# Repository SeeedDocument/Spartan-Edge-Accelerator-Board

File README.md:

---
name: Spartan Edge Accelerator Board
category: Platform
bzurl: 
oldwikiname: 
prodimagename:
surveyurl: 
sku: 102030005
tags:
---

The Spartan Edge Accelerator Board (SEA Board in short) is a lightweight FPGA development board, it is based on the Xilinx Spartan-7 chip and follows the Arduino shield form factor. Hence, you can use it as an Arduino shield to driver an LCD and a camera or as a stand-alone FPGA development board. Besides, with the help of on-board ESP32 chip, the SEA board also enables your Arduino with WiFi and Bluetooth function.

**Spartan-7** is the newest and most cost-effective FPGA chip among Xilinx’s FPGA family, offers the best in class performance per watt. 

On top of that, we provide the full FPGA APIs for Arduino, which means Arduino users are able to use the FPGA function without knowing anything about FPGA. This board will broaden Arduino’s capability in many ways like simple image processing and computer vision application, signal encryption and decryption, and signal sampling and processing. 

## Features

- Full FPGA APIs for Arduino
- Stand alone mode/Arduino Shield mode
- On-board WiFi and bluetooth 4.1 with BLE
- On-board 8 bit ADC
- On-board 6 axis Accelerometer and Gyroscope
- On-board Grove Connector(I2C/D2)

## Specification

|Parameter|Value|
|---|---|
|**FPGA**||
|FPGA Chip|Spartan-7 XC7S15|
|Logic Cells|12,800|
|Slics|2000|
|CLB Flip-Flops|16,000|
|Max. Distributed RAM (Kb)|150|
|Block RAM/FIFO w / ECC (36 kb each)|10|
|Total Block RAM (Kb)|360|
|Clock Mgmt Tiles (1 MMCM + 1 PLL)|2|
|DSP Slices|20|
|**Wireless**||
|Wireless Chip|Espressif ESP32-D0WDQ6|
|WiFi |802.11 b/g/n 2.4GHz|
|Bluetooth|Bluetooth 4.1 with BLE|
|**Peripheral**||
|Video|Mini HDMI x1|
|Camera|CSI/MIPI interface x1 (compatible with Raspberry Pi Camera V1 - OV5640)|
|SD card|Micro SD/TF card slot x1|
|FPGA GPIO|10 pins header (IO9~IO0)|
|Arduino GPIO|32 pins header (Arduino form factor)|
|Grove|Grove Connector x2 (I2C/D2)|
|LED|Monochrome LED x2<br>RGB LED x2|
|Button|Boot x1<br> Reset x1<br> FPGA Reset x1 <br> User x2|
|Switch|Power Mode Switch x1<br>5-Channel DIP Switch x1|
|**Power**||
|Operating Voltage|5V|
|Power Mode|USB Type C 5V<br>VIN 5V<br>Arduino VCC 5V|
|**Others**||
|ADC|8 bit ADC1173|
|Accelerometer and Gyroscope|6-axis LSM6DS3TR |

## Hardware Overview

<div align="center">
<figure>
  <a href="https://raw.githubusercontent.com/SeeedDocument/Spartan-Edge-Accelerator-Board/master/img/Spartan-Edge-Accelerater-Board-v1.0-pin.jpg" target="_blank">
  <figcaption><b>Figure 1</b>. <i>Seeed relay quick selection diagram, you can click the diagram to view the original file</i></figcaption></a>
</figure>
</div>

|Number|Detail|
|-----|-------|
|1.|FPGA : XC7S15-1FTGB196C|
|2.|WiFi/Bluetooth : ESP32-D0WDQ6|
|3.|6-axis Accelerometer and Gyroscope : LSM6DS3TR |
|4.|DAC : DAC7311IDCKR|
|5.|Buck-DCDC : TPS62130|
|6.|USB-to-UART : CP2102-GMR|
|7.|USB : Type-C |
|8.|Mini HDMI|
|9.|CSI Interface ：MIPI Camera (compatible with Raspberry Pi Camera V1 - OV5640)|
|10.|Arduino Header : Compatible with Arduino UNO|
|11.|DIP Switchs :|K1-K4 user switchs<br>K5 Switch FPGA Programming Mode  ->JTAG:|
|12.||

based on Spartan-7, one of the newest and most cost-effective chip among Xilinx’s FPGA family. 

<p style=":center"></p>

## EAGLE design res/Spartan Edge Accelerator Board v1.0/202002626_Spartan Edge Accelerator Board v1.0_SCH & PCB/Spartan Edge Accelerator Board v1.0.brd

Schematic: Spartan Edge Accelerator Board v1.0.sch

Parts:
ANT1: ACA-5036; ANT3-SMD-5.2X3.7X0.7MM
BOOT: SKRPABE010; SW4P-SMD-4.5X3.2X2.5MM
BUTTON1, BUTTON2: BUTTON; SW4P-SMD-4.5X3.2X2.5MM
C1, C10, C11, C13, C14, C16, C22, C23, C25, C26, C27, C28, C29, C30, C31, C32, C33, C34, C35, C36, C37, C38, C39, C50, C51, C59, C60, C63, C64, C65, C66, C67, C68, C75: 1uF; C0402
C2, C3: 10pF; C0402
C4, C5, C6, C7, C8, C9, C12, C15, C17, C24, C72, C73, C78, C81, C84, C99, C101, C103, C105: 100nF; C0402
C18, C57, C77, C85, C94: 100nF; C0603
C20: 3.3nF; C0402
C21: 10nF; C0402
C40, C41, C42, C45, C48, C49, C52, C58, C61, C62, C69, C70: 22uF; C1206
C43, C44, C46: 470nF; C0402
C47, C55, C56, C74, C76: 10uF; C0805
C53, C54: 33nF; C0603
C71, C79, C80, C83, C86, C87, C95, C96, C98, C100: DNP; C0402
C82, C102, C104, C106: 10uF; C0603
C90, C93, C97: DNP; C0603
C91, C92: 4.7uF; C0603
D1, D2, D5, D6, D7, D8, D9, D11, D12, D13, D14, D15, D16, D17, D21: ESDPSA0402V05; ESD-0402
D3, D18: Green; LED-0402
D4: RB160M-60TR; SOD-123
D10: BAS16XV2T1G; SOD-523
D19, D20: Red; LED-0402
F1: 1000mA; F1206
F2: 1812L160/12; F1812
FB1, FB2, FB3: 220R/2A; F0603
FB4, FB5: 120R/1.3A; F0402
FB6: BLM21PG331SN1D; F0805
FB7, FB8, FB9: 120R/2A; F0603
FPGA_RST: BUTTON; SW4P-SMD-4.5X3.2X2.5MM
FR1, FR2, FR3, FR4, FR5, FR6: SEEEDSTUDIO-OPEN-SCH-FRAME-BIG; SEEEDSTUDIO-PCB-FRAME
J1: 4PIN-2.54; H4-2.54
J2, J4: 320110033; HW4-2.0
J3: SCHA5B0200; MICRO-SD9+7P-SMD-15X14.5X1.5
J5: 2*3pin; H2X3-2.54
J6: FPC 15pins; H2X15-SMD-1MM
J8: 6PIN-2.54; H6-2.54-C65D35MIL
J9: Mini HDMI; HDMI-19+4P-0.4-11.2X7.5MM
J10: DNP; H10-2.54
J15: HEADER-3P-2.54; H3-2.54
L1, L2: DNP; L0402
L3, L4, L5, L7: DNP; INT4-0.8-2X1.2MM
L6: VLC5045T-2R2N; INT2-SMD-4.8X4.8X3MM
L15: SRF2012-900YA; INT4-0.85-2X1.25X1.2MM
LED1, LED2: SK6805; LED-4P-SMD-2.7X2.4MM
Q1: CJ2102; SOT-323
Q2, Q3: CJ3407; SOT-23
Q4, Q5: MMBT3904; SOT-23
R1, R33, R35, R118, R120, R122, R124, R165: 20k; R0402
R2, R17, R20, R38, R94, R95, R97, R104, R105, R106, R116, R125, R127, R146, R147, R149, R150, R181, R182, R184, R186, R187: DNP; R0402
R3, R6, R7, R16, R23, R24, R25, R26, R27, R37, R47, R58, R66, R93: 0R; R0402
R4, R5, R9, R13, R14, R18, R19, R32, R34, R36, R48, R67, R71, R85, R96, R114, R117, R119, R121, R123, R126, R133, R145, R164, R183, R185: 10k; R0402
R8, R21, R40, R41, R42, R43, R53, R54, R55, R101, R102, R103, R144, R151, R171, R180: 4.7k; R0402
R10, R12, R84, R107, R108, R109, R110, R111, R112, R113, R115, R140, R141, R142, R143: 33R; R0402
R11, R62: 0R; R0603
R15, R22: 5.1k; R0402
R28, R29, R68, R69: 100R; R0402
R30, R31, R44, R45, R46, R153, R155, R157, R159, R161, R163, R167, R173, R175, R177, R179: 2k; R0402
R39: 200k; R0402
R49, R50, R51, R52, R56, R57, R65, R70, R82, R83, R92, R152, R154, R156, R158, R160, R162, R166, R172, R174, R176, R178: 1k; R0402
R59, R60, R63, R64, R130: 100k; R0402
R61: 100k; R0603
R72, R73, R74, R75, R76, R77, R78, R79: 49.9R; R0402
R80, R81, R86, R87, R88, R89, R90, R91: 100nF; R0603
R98, R99, R100: 150R_1%; R0402
R128, R129: 100R_1%; R0402
R134: 536k_1%; R0603
R135: 100K_1%; R0603
R148: DNP; R1206
RST: SKRPADE010; SW4P-SMD-4.5X3.2X2.5MM
SW1: 311010004; SW6-2.54-9.0X3.5X3.2+2.0MM
SW2: DG2788A; MINI-QFN16-0.4-2.6X1.8X0.55MM
SW4: SWITCH-5BIT-DSHP05TSGER; 10P-SMD-7.95X5.4X2.3MM
TP1, TP2: TEST-POINT-35; TP_3535
TP5: TEST-POINT'4545'; TP-D45MIL
U1: XC7S15-1FTGB196C; FTGB196-1.0-15X15X1.46MM
U2: ESP32-D0WDQ6; QFN48G-0.4-6X6MM
U3: W25Q32JVZPIG; SOIC8-1.27-5X4MM
U4: ADC1173; TSSOP24-0.65-7.8X4.4MM
U5: CP2102-GMR; QFN28
U6: DAC7311IDCKR; SC-70-6
U7: CJ1117-3V3; SOT-223
U8: XC6221B102MR; SOT-23-5
U9: RT9013-18GB; SOT-23-5
U10: Arduino pins; ARDUINO-32P
U11: TPS62130; VQFN16-0.5-3X3X1MM
U12: LSM6DS3TR; LGA14L_DOT_INDICATOR
U13: PCA9306DQER; X2SON8-0.35-1.4X1X0.37MM
U15, U16: RCLAMP0524P; ESD10P-0.5-2.5X1X0.58MM
U17, U18: TXS0104EPWR; TSSOP14-0.65-5X4.4MM
USB2: 320010516/ ST-USB-1410; USB2.0-TYPE-C
X2: O3225100MEDA4SC; X4-SMD-3.2X2.5X1MM
X3: XTL581100-M118-080; X4-SMD-2.5X2.0X1.0MM

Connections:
3V3_IMU: C84.1, C97.2, C99.1, FB5.2, R114.2, R117.2, U12.5 (VDDIO), U12.8 (VDD)
ADC_CLK: U1.C5 (IO_L6P_T0_34), U4.12 (CLK)
ADC_D0: U1.J3 (IO_L17N_T2_34), U4.3 (DO(LSB))
ADC_D1: U1.J2 (IO_L15P_T2_DQS_34), U4.4 (D1)
ADC_D2: U1.D12 (IO_L8P_T1_D11_14), U4.5 (D2)
ADC_D3: U1.E12 (IO_L7N_T1_D10_14), U4.6 (D3)
ADC_D4: U1.F12 (IO_L7P_T1_D09_14), U4.7 (D4)
ADC_D5: U1.C11 (IO_L6P_T0_FCS_B_14), U4.8 (D8)
ADC_D6: U1.H11 (IO_L13P_T2_MRCC_14), U4.9 (D6)
ADC_D7: U1.H12 (IO_L13N_T2_MRCC_14), U4.10 (D7(MSB))
ADC_EN: U1.J4 (IO_L17P_T2_34), U4.1 (!OE)
ADC_IN: C87.1, J1.1, U4.19 (VIN)
AGND: C53.1, R11.1, R135.2, U11.6 (AGND)
AR_3V3_EN: Q2.1 (G), Q3.1 (G), R48.1, U1.L13 (IO_L16N_T2_D31_14)
AR_A0: R32.2, U10.19 (PC0/AD0/D14)
AR_A1: R34.2, U10.20 (PC1/AD1/D15)
AR_A2: R36.2, U10.21 (PC2/AD2/D16)
AR_A3: R119.2, U10.22 (PC3/AD3/D17)
AR_A4: R121.2, U10.23 (PC4/AD4/D18/SDA)
AR_A5: R123.2, U10.24 (PC5/AD5/D19/SCL)
AR_D0/RX: R150.1, U10.1 (PD0/D0/RX), U17.11 (B3)
AR_D1/TX: R146.1, U10.2 (PD1/D1/TX), U17.10 (B4)
AR_D2: R152.2, U10.3 (PD2/D2/INT0)
AR_D3: R154.2, U10.4 (PD3/D3/INT1/PWM)
AR_D4: R156.2, U10.5 (PD4/D4)
AR_D5: R158.2, U10.6 (PD5/D5/PWM)
AR_D6: R172.2, U10.7 (PD6/D6/PWM)
AR_D7: R174.2, U10.8 (PD7/D7)
AR_D8: R176.2, U10.9 (PB0/D8)
AR_D9: R178.2, U10.10 (PB1/D9/PWM)
AR_D10: R160.2, U10.11 (PB2/D10/SS/PWM)
AR_D11: R162.2, U10.12 (PB3/D11/MOSI/PWM)
AR_D12: R164.2, U10.13 (PB4/D12/MISO)
AR_D13: R166.2, U10.14 (PB5/D13/SCK)
AR_MISO: J5.1, U18.11 (B3)
AR_MOSI: J5.5, U18.12 (B2)
AR_RESET: J5.3, R187.2, U10.30 (RESET), U18.10 (B4)
AR_SCK: J5.2, U18.13 (B1)
AR_SCL: R151.1, U10.18 (SCL), U17.12 (B2)
AR_SDA: R171.1, U10.17 (SDA), U17.13 (B1)
CHIP_PU: Q4.3 (C), R5.1, RST.1 (A0), RST.2 (A1), U2.9 (CHIP_PU)
D+: D1.2, L15.3, USB2.A6 (A6/DP1), USB2.B6 (B6/DP2)
D-: D2.2, L15.2, USB2.A7 (A7/DN1), USB2.B7 (B7/DN2)
DAC_DIN: U1.L1 (IO_L18N_T2_34), U6.3 (DIN)
DAC_OUT: C86.1, J1.4, U6.6 (VOUT)
DAC_SCLK: U1.M1 (IO_L18P_T2_34), U6.2 (SCLK)
DAC_SYNC: U1.N1 (IO_L20N_T3_34), U6.1 (!SYNC)
ESP_A4: R121.1, R122.1, SW2.11 (NO1)
ESP_A5: R123.1, R124.1, SW2.15 (NO2)
ESP_AR_A0: R32.1, R33.1, U2.5 (SENSOR_VP)
ESP_AR_A1: R34.1, R35.1, U2.6 (SENSOR_CAPP)
ESP_AR_A2: R36.1, R118.1, U2.7 (SENSOR_CAPN)
ESP_AR_A3: R119.1, R120.1, U2.8 (SENSOR_VN)
ESP_FPGA-TYPE: R125.1, R126.2, U2.11 (VDET_2)
ESP_QSPI_CLK: R84.2, U2.35 (GPIO18)
ESP_QSPI_CS: R115.2, U2.34 (GPIO5)
ESP_QSPI_D: R141.2, U2.36 (GPIO23)
ESP_QSPI_HD: R142.2, U2.42 (GPIO21)
ESP_QSPI_Q: R140.2, U2.38 (GPIO19)
ESP_QSPI_WP: R143.2, U2.39 (GPIO22)
ESP_SCL_A5: SW2.16 (COM2), U2.13 (32K_XN)
ESP_SDA_A4: SW2.12 (COM1), U2.12 (32K_XP)
FLASH_SCK: R29.2, U2.31 (SD_CLK), U3.6 (CLK)
FLASH_SCS: R28.2, R104.2, U2.30 (SD_CMD), U3.1 (/CS)
FLASH_SDI: R69.2, U2.33 (SD_DATA_1), U3.5 (DIO)
FLASH_SDO: R68.2, U2.32 (SD_DATA_0), U3.2 (DO)
FLASH_SHD: R127.2, TP1.T, U2.28 (SD_DATA_2), U3.7 (/HOLD)
FLASH_SWP: R116.2, TP2.T, U2.29 (SD_DATA_3), U3.3 (/WP)
FLASH_VDD: R2.2, U2.26 (VDD_SDIO)
FPGA_AR_D0/RX: R181.1, U1.A12 (IO_L4P_T0_D04_14), U17.4 (A3)
FPGA_AR_D1/TX: R182.1, U1.C12 (IO_L6N_T0_D08_VREF_14), U17.5 (A4)
FPGA_AR_D2: J2.1, R152.1, R153.1, U1.A10 (IO_L3N_T0_DQS_EMCCLK_14)
FPGA_AR_D3: J2.2, R154.1, R155.1, U1.B6 (IO_0_34)
FPGA_AR_D4: R156.1, R157.1, U1.A5 (IO_L4N_T0_34)
FPGA_AR_D5: R158.1, R159.1, U1.B5 (IO_L4P_T0_34)
FPGA_AR_D6: R172.1, R173.1, U1.A4 (IO_L2P_T0_34)
FPGA_AR_D7: R174.1, R175.1, U1.A3 (IO_L2N_T0_34)
FPGA_AR_D8: R176.1, R177.1, U1.B3 (IO_L3P_T0_DQS_34)
FPGA_AR_D9: R178.1, R179.1, U1.A2 (IO_L3N_T0_DQS_34)
FPGA_AR_D10: R160.1, R161.1, U1.B2 (IO_L5P_T0_34)
FPGA_AR_D11: R162.1, R163.1, U1.B1 (IO_L5N_T0_34)
FPGA_AR_D12: R164.1, R165.1, U1.H1 (IO_L14N_T2_SRCC_34)
FPGA_AR_D13: R166.1, R167.1, U1.H2 (IO_L14P_T2_SRCC_34)
FPGA_AR_DET: R49.2, R71.2, U1.B11 (IO_L1P_T0_D00_MOSI_14)
FPGA_AR_MISO: U1.L5 (IO_25_34), U18.4 (A3)
FPGA_AR_MOSI: U1.M5 (IO_L23P_T3_34), U18.3 (A2)
FPGA_AR_OE1: R183.2, R184.2, U1.N4 (IO_L24N_T3_34), U17.8 (OE)
FPGA_AR_OE2: R185.2, U1.M3 (IO_L19P_T3_34), U18.8 (OE)
FPGA_AR_RESET: R186.1, U1.K4 (IO_L16P_T2_34), U18.5 (A4)
FPGA_AR_SCK: U1.H13 (IO_L14P_T2_SRCC_14), U18.2 (A1)
FPGA_CAM_CN: J6.8, J6.23, R100.1, U1.F11 (IO_L12N_T1_MRCC_14)
FPGA_CAM_CP: J6.9, J6.24, R100.2, U1.G11 (IO_L12P_T1_MRCC_14)
FPGA_CAM_DN1: J6.5, J6.20, R99.1, U1.P11 (IO_L24N_T3_D16_14)
FPGA_CAM_DNO: J6.2, J6.17, R98.1, R128.1, U1.J12 (IO_L17N_T2_D29_14)
FPGA_CAM_DP1: J6.6, J6.21, R99.2, U1.P10 (IO_L24P_T3_D17_14)
FPGA_CAM_DPO: J6.3, J6.18, R98.2, R129.1, U1.J11 (IO_L17P_T2_D30_14)
FPGA_CAM_GPIO1: J6.12, J6.27, U1.M11 (IO_L20P_T3_D24_14)
FPGA_CAM_RST: J6.11, J6.26, R38.1, U1.M12 (IO_L20N_T3_D23_14)
FPGA_CAM_SCL: J6.13, J6.28, R30.1, U1.K11 (IO_L19P_T3_D26_14)
FPGA_CAM_SDA: J6.14, J6.29, R31.1, U1.K12 (IO_L19N_T3_D25_VREF_14)
FPGA_CCLK: R24.2, U1.A8 (CCLK_0)
FPGA_CCLK_ESP: R24.1, U2.27 (GPIO17)
FPGA_CONFIG_DIN: R27.2, U1.B12 (IO_L1N_T0_D01_DIN_14)
FPGA_CONFIG_DIN_ESP: R27.1, U2.16 (GPIO27)
FPGA_DONE: D20.+, R26.2, R55.2, U1.P9 (DONE_0)
FPGA_DONE_ESP: R26.1, U2.10 (VDET_1)
FPGA_ESP_IN1/2: R133.1, SW2.14 (IN1_2), U1.H3 (IO_L13N_T2_MRCC_34)
FPGA_ESP_IO5: R28.1, U1.E13 (IO_L10N_T1_D15_14)
FPGA_ESP_IO6: R29.1, U1.F14 (IO_L9N_T1_DQS_D13_14)
FPGA_ESP_IO7: R68.1, U1.F13 (IO_L10P_T1_D14_14)
FPGA_ESP_IO8: R69.1, U1.G14 (IO_L9P_T1_DQS_14)
FPGA_ESP_SCL: J4.1, R180.1, SW2.1 (NC2), U1.P12 (IO_L22P_T3_D21_14), U12.13 (SCL), U17.3 (A2)
FPGA_ESP_SDA: J4.2, R144.1, SW2.13 (NC1), U1.P13 (IO_L22N_T3_D20_14), U12.14 (SDA), U17.2 (A1)
FPGA_HDMI_SCL: R42.2, U1.F3 (IO_L8P_T1_34), U13.3 (SCL1)
FPGA_HDMI_SDA: R43.2, U1.F2 (IO_L8N_T1_34), U13.4 (SDA1)
FPGA_HDMI_TCK+: L7.4 (2), R78.2, R90.2, U1.G4 (IO_L12P_T1_MRCC_34)
FPGA_HDMI_TCK-: L7.3, R79.2, R91.2, U1.F4 (IO_L12N_T1_MRCC_34)
FPGA_HDMI_TD0+: L5.4 (2), R76.2, R88.2, U1.G1 (IO_L9P_T1_DQS_34)
FPGA_HDMI_TD0-: L5.3, R77.2, R89.2, U1.F1 (IO_L9N_T1_DQS_34)
FPGA_HDMI_TD1+: L4.4 (2), R74.2, R86.2, U1.E2 (IO_L10P_T1_34)
FPGA_HDMI_TD1-: L4.3, R75.2, R87.2, U1.D2 (IO_L10N_T1_34)
FPGA_HDMI_TD2+: L3.4 (2), R72.2, R80.2, U1.D1 (IO_L11P_T1_SRCC_34)
FPGA_HDMI_TD2-: L3.3, R73.2, R81.2, U1.C1 (IO_L11N_T1_SRCC_34)
FPGA_INTB: R25.2, R54.2, U1.P8 (INIT_B_0)
FPGA_INTB_ESP: R25.1, U2.15 (GPIO26)
FPGA_IO0: J10.1, U1.N14 (IO_L21P_T3_DQS_14)
FPGA_IO1: J10.2, U1.M14 (IO_L21N_T3_DQS_D22_14)
FPGA_IO2: J10.3, U1.C4 (IO_L6N_T0_VREF_34)
FPGA_IO3: J10.4, U1.B13 (IO_L5P_T0_D06_14)
FPGA_IO4: J10.5, U1.N10 (IO_L23P_T3_D19_14)
FPGA_IO5: J10.6, U1.M10 (IO_25_14)
FPGA_IO6: J10.7, U1.B14 (IO_L5N_T0_D07_14)
FPGA_IO7: J10.8, U1.D3 (IO_L1P_T0_34)
FPGA_IO8: J10.9, U1.P5 (IO_L24P_T3_34)
FPGA_IO9: J10.10, U1.E11 (IO_0_14)
FPGA_IO10: BUTTON1.1 (A0), BUTTON1.2 (A1), C96.1, R102.2, U1.C3 (IO_L1N_T0_34)
FPGA_IO11: BUTTON2.1 (A0), BUTTON2.2 (A1), C98.1, R103.2, U1.M4 (IO_L23N_T3_34)
FPGA_IO12: R128.2, U1.C10 (IO_L2N_T0_D03_14)
FPGA_IO13: R129.2, U1.D10 (IO_L2P_T0_D02_14)
FPGA_K1: R64.1, SW4.1, U1.M2 (IO_L19N_T3_VREF_34)
FPGA_K2: R63.1, SW4.2, U1.L2 (IO_L22N_T3_34)
FPGA_K3: R60.1, SW4.3, U1.L3 (IO_L22P_T3_34)
FPGA_K4: R59.1, SW4.4, U1.K3 (IO_L16N_T2_34)
FPGA_LED1: D18.+, U1.J1 (IO_L15N_T2_DQS_34)
FPGA_LED2: D19.+, U1.A13 (IO_L4N_T0_D05_14)
FPGA_M0: R57.2, U1.M7 (M0_0)
FPGA_M1: R130.1, SW4.5, U1.M8 (M1_0)
FPGA_M2: R56.2, U1.M9 (M2_0)
FPGA_PROGRAM: R23.2, R53.2, U1.L7 (PROGRAM_B_0)
FPGA_PROGRAM_ESP: R23.1, U2.14 (GPIO25)
FPGA_QSPI_CLK: R84.1, U1.H14 (IO_L14N_T2_SRCC_14)
FPGA_QSPI_CS: R115.1, U1.M13 (IO_L15P_T2_DQS_RDWR_B_14)
FPGA_QSPI_D: R141.1, U1.P2 (IO_L20P_T3_34)
FPGA_QSPI_HD: R142.1, U1.D13 (IO_L8N_T1_D12_14)
FPGA_QSPI_Q: R140.1, U1.L14 (IO_L15N_T2_DQS_DOUT_CSO_B_14)
FPGA_QSPI_WP: R143.1, U1.J13 (IO_L18P_T2_D28_14)
FPGA_RGB: LED1.3 (DIN), U1.N11 (IO_L23N_T3_D18_14)
FPGA_RST: C95.1, FPGA_RST.1 (A0), FPGA_RST.2 (A1), R101.2, U1.D14 (IO_L11P_T1_SRCC_14)
FPGA_TCK: J8.4, U1.A7 (TCK_0)
FPGA_TDI: J8.6, U1.P7 (TDI_0)
FPGA_TDO: J8.5, U1.P6 (TDO_0)
FPGA_TMS: J8.3, U1.M6 (TMS_0)
GND: ANT1.2 (GND1), ANT1.3 (GND2), BOOT.3 (B0), BOOT.4 (B1), BUTTON1.3 (B0), BUTTON1.4 (B1), BUTTON2.3 (B0), BUTTON2.4 (B1), C1.1, C2.1, C3.1, C4.2, C5.2, C6.2, C7.2, C8.2, C9.2, C10.2, C11.2, C12.2, C13.1, C14.1, C15.1, C16.1, C17.1, C18.1, C21.2, C22.2, C23.2, C24.2, C25.2, C26.2, C27.2, C28.2, C29.2, C30.2, C31.2, C32.2, C33.2, C34.2, C35.2, C36.2, C37.2, C38.2, C39.2, C40.2, C41.2, C42.2, C43.2, C44.2, C45.2, C46.2, C47.1, C48.1, C49.1, C50.2, C51.2, C52.1, C54.1, C55.1, C56.1, C57.1, C58.1, C59.2, C60.2, C61.1, C62.1, C63.2, C64.2, C65.2, C66.2, C67.2, C68.2, C69.1, C70.1, C71.2, C72.2, C73.2, C74.1, C75.2, C76.1, C77.1, C78.2, C79.2, C80.2, C81.2, C82.1, C83.2, C84.2, C85.1, C86.2, C87.2, C91.1, C92.1, C94.1, C95.2, C96.2, C97.1, C98.2, C99.2, C100.2, C101.1, C102.2, C103.1, C104.2, C105.2, C106.1, D1.1, D2.1, D3.-, D5.1, D6.1, D7.1, D8.1, D9.1, D11.1, D12.1, D13.1, D14.1, D15.1, D16.1, D17.1, D21.2, FB7.1, FB8.2, FB9.2, FPGA_RST.3 (B0), FPGA_RST.4 (B1), J1.2, J1.3, J2.4, J3.6 (VSS), J3.9 (GND), J4.4, J5.4, J6.1, J6.4, J6.7, J6.10, J6.16, J6.19, J6.22, J6.25, J8.2, J9.1 (TMDS_DATA2_SHIELD), J9.4 (TMDS_DATA1_SHIELD), J9.7 (TMDS_DATA0_SHIELD), J9.10 (TMDS_CLOCK_SHIELD), J9.13 (DDC/CEC_GROUND), L1.1, L2.1, LED1.2 (VSS), LED2.2 (VSS), Q1.2 (S), R6.1, R7.2, R11.2, R15.2, R19.1, R20.1, R22.2, R33.2, R35.2, R38.2, R44.1, R45.1, R46.1, R59.2, R60.2, R63.2, R64.2, R65.2, R67.1, R71.1, R118.2, R120.2, R122.2, R124.2, R126.1, R130.2, R133.2, R145.1, R149.1, R153.2, R155.2, R157.2, R159.2, R161.2, R163.2, R165.2, R167.2, R173.2, R175.2, R177.2, R179.2, R184.1, R185.1, RST.3 (B0), RST.4 (B1), SW2.2 (GND), U1.A1 (GND), U1.A6 (GND), U1.A9 (GND), U1.A11 (GND), U1.A14 (GND), U1.B4 (GND), U1.B7 (GND), U1.B8 (NC), U1.B9 (GND), U1.C2 (GND), U1.C6 (GND), U1.C7 (GND), U1.C8 (GND), U1.C9 (GND), U1.C13 (GND), U1.D5 (GND), U1.D7 (GND), U1.D9 (GND), U1.D11 (GND), U1.E1 (GND), U1.E3 (GND), U1.E6 (GND), U1.E8 (GND), U1.E10 (GND), U1.E14 (GND), U1.F5 (GND), U1.F7 (NC), U1.F9 (GND), U1.G3 (GND), U1.G6 (GND), U1.G7 (NC), U1.G8 (NC), U1.G10 (GND), U1.G12 (GND), U1.H5 (GND), U1.H7 (NC), U1.H8 (NC), U1.H9 (GND), U1.J6 (GND), U1.J7 (DXN_0), U1.J8 (DXP_0), U1.J10 (GND), U1.K1 (GND), U1.K5 (GND), U1.K7 (GND), U1.K9 (GND), U1.K14 (GND), U1.L4 (GND), U1.L6 (GND), U1.L8 (GND), U1.L10 (GND), U1.L11 (GND), U1.N3 (GND), U1.N5 (GND), U1.N9 (GND), U1.N12 (GND), U1.P1 (GND), U1.P14 (GND), U2.PAD (GND), U3.4 (GND), U4.2 (DVSS), U4.23 (VRB), U4.24 (DVSS), U5.3 (GND), U5.PAD, U7.1 (GND), U8.2 (VSS), U9.2 (VSS), U10.15 (GND), U10.26 (GND), U10.27 (GND), U11.7 (FSW), U11.8 (DEF), U11.15 (PGND), U11.16 (PGND), U11.PAD, U12.2 (SDX), U12.3 (SCX), U12.6 (GND), U12.7 (GND), U13.1 (GND), U15.3, U15.8, U16.3, U16.8, U17.7 (GND), U18.7 (GND), USB2.A1_B12 (A1/B12/GND), USB2.B1_A12 (B1/A12/GND), X2.2 (GND), X3.2 (GND), X3.4 (GND)
GPIO0: BOOT.1 (A0), BOOT.2 (A1), Q5.3 (C), R4.1, U2.23 (GPIO0)
HDMI_5V: C18.2, C94.2, D4.-, D6.2, J9.18 (+5V_POWER), R39.1, R40.1, R41.1
HDMI_CEC: D9.2, J9.14 (CEC), R93.2, U1.E4 (IO_L7P_T1_34)
HDMI_DDCSCL: D8.2, J9.15 (SCL), R40.2, U13.6 (SCL2)
HDMI_DDCSDA: D7.2, J9.16 (SDA), R41.2, U13.5 (SDA2)
HDMI_HPD: D5.2, J9.19 (HOT_PLUG_DETECT), R67.2, R70.1
HDMI_HPD_DET: Q1.3 (D), R21.1, U1.D4 (IO_L7N_T1_34)
HDMI_TCK+: J9.11 (TMDS_CLOCK+), L7.1, R90.1, U16.4, U16.7
HDMI_TCK-: J9.12 (TMDS_CLOCK-), L7.2 (4), R91.1, U16.5, U16.6
HDMI_TD0+: J9.8 (TMDS_DATA0+), L5.1, R88.1, U16.1, U16.10
HDMI_TD0-: J9.9 (TMDS_DATA0-), L5.2 (4), R89.1, U16.2, U16.9
HDMI_TD1+: J9.5 (TMDS_DATA1+), L4.1, R86.1, U15.4, U15.7
HDMI_TD1-: J9.6 (TMDS_DATA1-), L4.2 (4), R87.1, U15.5, U15.6
HDMI_TD2+: J9.2 (TMDS_DATA2+), L3.1, R80.1, U15.1, U15.10
HDMI_TD2-: J9.3 (TMDS_DATA2-), L3.2 (4), R81.1, U15.2, U15.9
IMU_AD: R114.1, U1.J14 (IO_L18N_T2_D27_14), U12.1 (SDO/SA0)
IMU_INT2: U1.L12 (IO_L16P_T2_CSI_B_14), U12.9 (INT2)
unnamed: Q2.3 (D), Q3.3 (D)
unnamed: C2.2, R47.2, X3.3 (X2)
unnamed: R22.1, USB2.A5 (A5/CC1)
unnamed: R16.1, X2.3 (OUT)
unnamed: R15.1, USB2.B5 (B5/CC2)
unnamed: R117.1, U12.12 (CS)
unnamed: C12.1, J6.15, J6.30, R37.1
unnamed: R10.2, U5.26 (TXD)
unnamed: D10.-, R93.1
unnamed: C20.2, R1.2, U2.47 (CAP2)
unnamed: C20.1, C21.1, R1.1, U2.48 (CAP1)
unnamed: L1.2, R58.2, U2.2 (LNA_IN)
unnamed: ANT1.1 (D), L2.2, R58.1
unnamed: C24.1, R2.1, R3.1, U3.8 (VCC)
unnamed: L15.1, U5.5 (D-)
unnamed: C26.1, FB2.2, U4.14 (AVDD), U4.15 (AVDD), U4.18 (AVDD)
unnamed: L15.4, U5.4 (D+)
unnamed: Q5.1 (B), R14.1
unnamed: C13.2, R8.1, U5.9 (!RST)
unnamed: C83.1, R12.2, U5.25 (RXD)
unnamed: C29.1, FB3.1, U6.4 (AVDD/VREF)
unnamed: R50.1, R149.2, X2.1 (ENABLE)
unnamed: Q4.2 (E), R14.2, U5.24 (RTS)
unnamed: Q5.2 (E), R9.2, U5.28 (DTR)
unnamed: Q4.1 (B), R9.1
unnamed: R7.1, U6.5 (GND)
unnamed: D11.2, J3.10 (CD), R85.1, R107.2
unnamed: D3.+, R13.2
unnamed: FB6.2, SW1.CH1A, SW1.CH2A
unnamed: R51.2, SW4.7
unnamed: D4.+, F2.1
unnamed: Q1.1 (G), R70.2
unnamed: D12.2, J3.1 (DAT2), R94.1, R108.2
unnamed: R6.2, U4.20 (AVSS), U4.21 (AVSS)
unnamed: D13.2, J3.2 (DAT3/CD), R95.1, R109.2
unnamed: D14.2, J3.3 (CMD), R96.1, R110.2
unnamed: R39.2, U13.7 (VREF2), U13.8 (EN)
unnamed: R52.2, SW4.8
unnamed: R83.2, SW4.9
unnamed: C79.1, D15.2, J3.5 (CLK), R97.1, R111.2
unnamed: R92.2, SW4.10
unnamed: R82.2, SW4.6
unnamed: D16.2, J3.7 (DAT0), R105.1, R112.2
unnamed: D20.-, R46.2
unnamed: FB7.2, J9.P2 (SHELL2), J9.P3 (SHELL3)
unnamed: FB8.1, USB2.S1, USB2.S2, USB2.S5 (S1), USB2.S6 (S2)
unnamed: FB9.1, J3.13 (GND), J3.14 (GND)
unnamed: D18.-, R44.2
unnamed: D19.-, R45.2
unnamed: D17.2, J3.8 (DAT1), R106.1, R113.2
unnamed: C81.1, C82.2, FB4.2, J3.4 (VDD), R85.2, R94.2, R95.2, R96.2, R97.2, R105.2, R106.2
unnamed: R65.1, U1.B10 (IO_L3P_T0_DQS_PUDC_B_14)
unnamed: LED1.1 (DOUT), LED2.3 (DIN)
unnamed: C91.2, C92.2, LED1.4 (VDD), LED2.4 (VDD), R66.2
unnamed: R62.2, U11.13 (EN)
unnamed: C53.2, U11.9 (SS/TR)
unnamed: C74.2, C76.2, C77.2, FB6.1, L6.2, R134.1, U11.14 (VOS)
unnamed: L6.1, R61.2, U11.1 (SW), U11.2 (SW), U11.3 (SW)
unnamed: R61.1, U11.4 (PG)
unnamed: R134.2, R135.1, U11.5 (FB)
SDCARD_CCLK: C80.1, R111.1, U2.17 (MTMS)
SDCARD_CD: R107.1, U2.25 (GPIO16)
SDCARD_CMD: R110.1, U2.21 (MTDO)
SDCARD_D0: R112.1, U2.22 (GPIO2)
SDCARD_D1: R113.1, U2.24 (GPIO4)
SDCARD_D2: R108.1, U2.18 (MTDI)
SDCARD_D3: R109.1, U2.20 (MTCK)
SYSCLK: C71.1, R16.2, U1.H4 (IO_L13P_T2_MRCC_34)
U0RXD: C100.1, R10.1, U2.40 (U0RXD)
U0TXD: R12.1, U2.41 (U0TXD)
USB5V: D21.1, F1.2, USB2.A4_B9 (A4/B9/VBUS), USB2.B4_A9 (B4/A9/VBUS)
VCC_1V: C31.1, C32.1, C33.1, C34.1, C35.1, C36.1, C37.1, C38.1, C39.1, C41.1, C45.1, C46.1, C52.2, C58.2, C59.1, C60.1, U1.D6 (VCCINT), U1.D8 (VCCINT), U1.E5 (VCCBRAM), U1.E7 (VCCINT), U1.E9 (VCCINT), U1.F6 (VCCINT), U1.G5 (VCCBRAM), U1.G9 (VCCINT), U1.H6 (VCCINT), U1.J5 (VCCBRAM), U1.J9 (VCCINT), U1.K6 (VCCINT), U1.K8 (VCCINT), U8.5 (VOUT)
VCC_1V8: C40.1, C42.1, C43.1, C44.1, C61.2, C62.2, C63.1, C64.1, U1.F8 (NC), U1.F10 (VCCAUX), U1.H10 (VCCAUX), U1.K10 (VCCAUX), U1.L9 (VCCAUX), U9.5 (VOUT)
VCC_3V3: C25.1, C27.1, C28.1, C30.1, C48.2, C49.2, C50.1, C51.1, C72.1, C73.1, C75.1, C78.1, C85.2, C90.2, C105.1, C106.2, D10.+, FB1.2, FB2.1, FB3.2, FB4.1, FB5.1, J2.3, J4.3, J8.1, Q2.2 (S), R17.2, R18.2, R21.2, R30.2, R31.2, R37.2, R42.1, R43.1, R48.2, R50.2, R51.1, R52.1, R53.1, R54.1, R55.1, R56.1, R57.1, R66.1, R72.1, R73.1, R74.1, R75.1, R76.1, R77.1, R78.1, R79.1, R82.1, R83.1, R92.1, R101.1, R102.1, R103.1, R144.2, R147.2, R148.1, R180.2, R181.2, R182.2, R183.1, R186.2, U1.G2 (VCCO_34), U1.G13 (VCCO_14), U1.K2 (VCCO_34), U1.K13 (VCCO_14), U1.N2 (VCCO_34), U1.N6 (VCCO_0), U1.N7 (CFGBVS_0), U1.N8 (VCCO_0), U1.N13 (VCCO_14), U4.11 (DVDD), U4.13 (DVDD), U4.17 (VRT), U7.2 (OUT), U7.TER (OUT), U13.2 (VREF1), U17.1 (VCCA), U18.1 (VCCA), X2.4 (VDD)
VCC_3V3_AR: Q3.2 (S), R49.1, R148.2, U10.29 (3V3)
VCC_5V: C10.1, C11.1, C65.1, C66.1, C67.1, C68.1, C69.2, C70.2, C90.1, C93.1, C101.2, C102.1, C103.2, C104.1, F2.2, J15.1, R13.1, R146.2, R150.2, R151.2, R171.2, R187.1, SW1.COM1, SW1.COM2, SW2.10 (V+), U7.3 (IN), U8.1 (VIN), U8.3 (CE), U9.1 (VIN), U9.3 (CE), U17.14 (VCCB), U18.14 (VCCB)
VCC_5V_AR: J5.6, J15.2, U10.28 (5V)
VCC_ESP: C4.1, C5.1, C6.1, C7.1, C8.1, C9.1, C22.1, C23.1, FB1.1, R3.2, R4.2, R5.2, R104.1, R116.1, R125.2, R127.1, U2.1 (VDDA), U2.3 (VDD3P3), U2.4 (VDD3P3), U2.19 (VDD3P3_RTC), U2.37 (VDD3P3_CPU), U2.43 (VDDA), U2.46 (VDDA)
VDD: C16.2, C17.2, R8.2, U5.6 (VDD)
VERSION_1: R18.1, R20.2, U1.P4 (IO_L21P_T3_DQS_34)
VERSION_2: R17.1, R19.2, U1.P3 (IO_L21N_T3_DQS_34)
VERSION_3: R145.2, R147.1, U1.C14 (IO_L11N_T1_SRCC_14)
VIN: C47.2, C54.2, C55.2, C56.2, C57.2, C93.2, R62.1, TP5.T, U10.25 (VIN), U11.10 (AVIN), U11.11 (PVIN), U11.12 (PVIN)
VUSB: C1.2, C14.2, C15.2, F1.1, SW1.CH1B, SW1.CH2B, U5.7 (REGIN), U5.8 (VBUS)
XTAL_N: R47.1, U2.44 (XTAL_N)
XTAL_P: C3.2, U2.45 (XTAL_P), X3.1 (X1)

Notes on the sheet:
Vout(5.09)=0.8*((536/100)+1)
ESP32_FPGA--Program
FPGA_Crystal
FPGA_Download--Interface(2)
M[2~0]=101 JTAG Mode
M[2~0]=111 Slave serial Mode
Slave serial mode only supports .bin format document
Differential impedance:100 Ohm
ESD Protection Diodes close to HDMI Connector.
Close to Grove Interface
Layout Notes:
Place C79 R111 C80 Close to FPGA
Address Choose
Place R10 C100 Close to CP2102
Place R12 C83 Close to ESP32
In order to distinguish FPGA type
In order to distinguish hardware version
Sample version：000
changed the package
If you want to power to Arduino board,
you can use a jumper cap to connect (ON)
If the board is used as a main board，you can enable the Q2 and Q3
If the board is used as a shield board，you should disable the Q2 and Q3
v1.0
Initial Version
2019.08.08
weifeng.zeng
Official version： 001
Pull_Down --- XC7S15
Pull_UP --- XC7S25

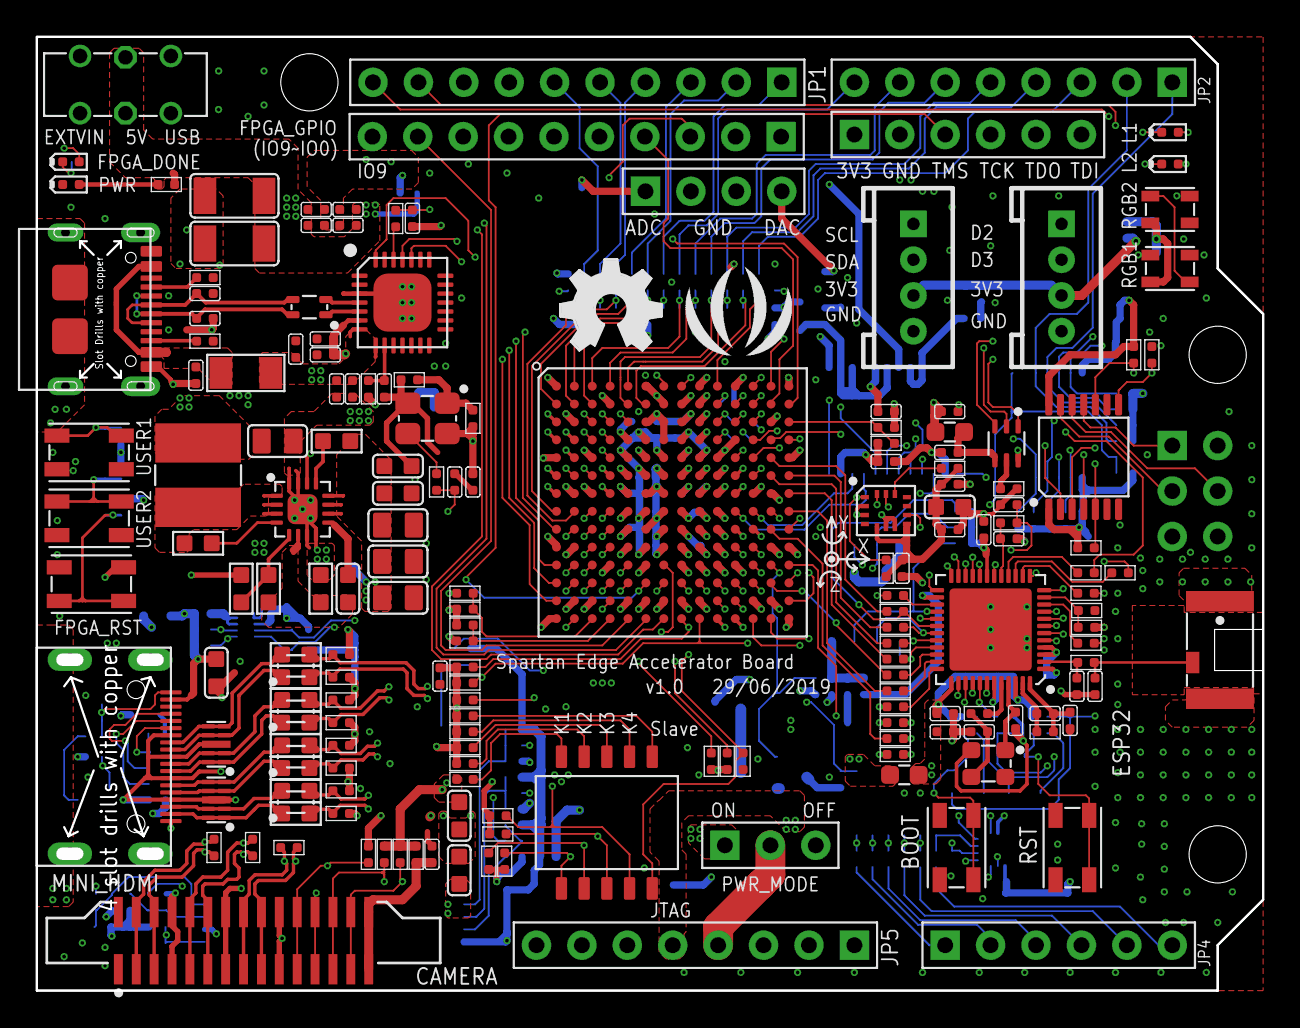
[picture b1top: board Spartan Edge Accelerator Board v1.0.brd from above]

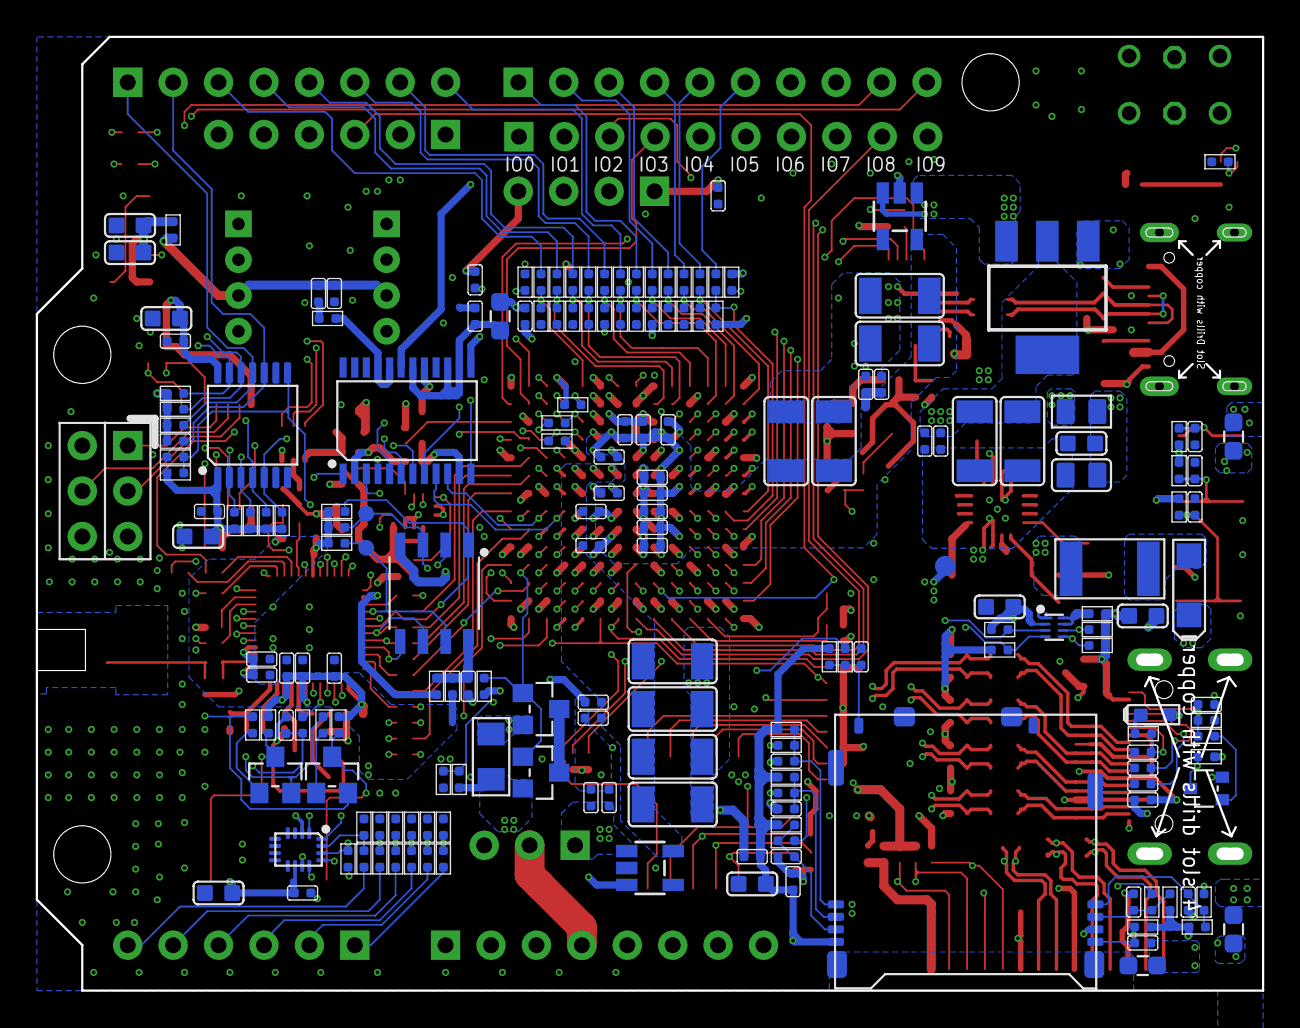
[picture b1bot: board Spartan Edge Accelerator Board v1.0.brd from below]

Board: 6 copper layers, 68.6 x 53.3 mm, 378 parts (192 on the bottom side), 266 nets.

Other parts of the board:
U$64: SEEED-SILK-TNAME-280*268MIL
U$65: OSHW_FILLX200_NOTEXT_TNAME

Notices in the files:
parts and their libraries:
moudle-new: This work is licensed under the Creative Commons Attribution 4.0 International License.
To view a copy of this license,visit:
http://creativecommons.org/licenses/by-sa/4.0
moudle-new: CC-BY-SA
